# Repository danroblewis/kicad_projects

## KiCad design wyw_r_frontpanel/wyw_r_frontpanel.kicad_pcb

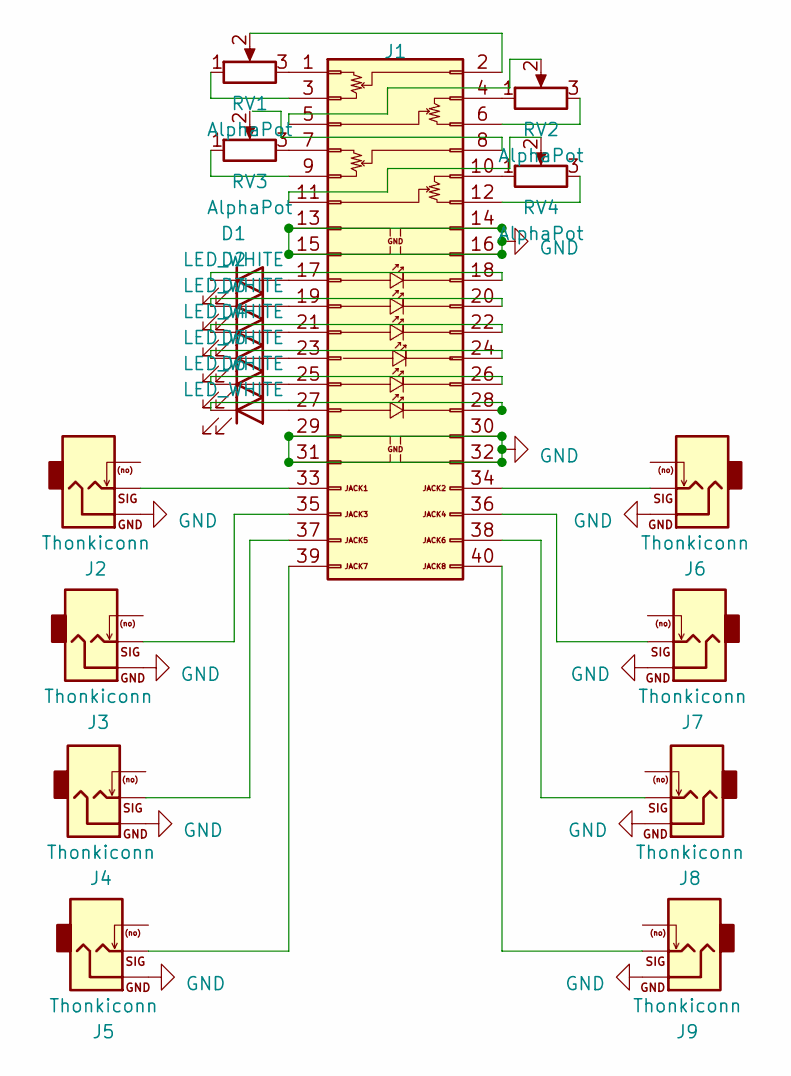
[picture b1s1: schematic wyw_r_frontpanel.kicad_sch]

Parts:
D1, D2, D3, D4, D5, D6: LED_WHITE; LED_0603_1608Metric; LCSC C2290
J1: female 02x20; PinSocket_2x20_P2.54mm_Vertical_SMD; lcsc C2685092
J2, J3, J4, J5, J6, J7, J8, J9: Thonkiconn; Jack_3.5mm_QingPu_WQP-PJ398SM_Vertical_CircularHoles
RV1, RV2, RV3, RV4: AlphaPot; Potentiometer_Alpha_RD901F-40-00D_Single_Vertical

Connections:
GND: J1.13, J1.14, J1.15, J1.16, J1.29, J1.30, J1.31, J1.32, J2.S, J3.S, J4.S, J5.S, J6.S, J7.S, J8.S, J9.S
unnamed: D1.2 (A), J1.17
unnamed: D1.1 (K), J1.18
unnamed: D2.2 (A), J1.19
unnamed: D2.1 (K), J1.20
unnamed: D3.2 (A), J1.21
unnamed: D3.1 (K), J1.22
unnamed: D4.2 (A), J1.23
unnamed: D4.1 (K), J1.24
unnamed: D5.2 (A), J1.25
unnamed: D5.1 (K), J1.26
unnamed: D6.2 (A), J1.27
unnamed: D6.1 (K), J1.28
unnamed: J1.1, RV1.3
unnamed: J1.2, RV1.2
unnamed: J1.3, RV1.1
unnamed: J1.4, RV2.1
unnamed: J1.5, RV2.2
unnamed: J1.6, RV2.3
unnamed: J1.7, RV3.3
unnamed: J1.9, RV3.1
unnamed: J1.10, RV4.1
unnamed: J1.11, RV4.2
unnamed: J1.12, RV4.3
unnamed: J1.33, J2.T
unnamed: J1.34, J6.T
unnamed: J1.35, J3.T
unnamed: J1.36, J7.T
unnamed: J1.37, J4.T
unnamed: J1.38, J8.T
unnamed: J1.39, J5.T
unnamed: J1.40, J9.T

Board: 2 copper layers, 19 parts (7 on the bottom side), 32 nets, no tracks yet.

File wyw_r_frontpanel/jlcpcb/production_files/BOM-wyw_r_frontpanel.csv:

Comment,Designator,Footprint,LCSC
LED_WHITE,"D1,D2,D3,D4,D5,D6",LED_0603_1608Metric,C2290
female 02x20,J1,PinSocket_2x20_P2.54mm_Vertical_SMD,C2685092
